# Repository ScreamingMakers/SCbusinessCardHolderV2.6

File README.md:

# SCbusinessCardHolderV2.6
V2.6 of the Screaming Circuits open source, hackable, electronic business card holder 

The Screaming Circuits business card holder is a multi-function device intended for your amusement and as a demonstration of our workmanship.

It has 19 LEDs along the bottom of the board, with 16 being broken out to optional headers - for your hacking pleasure. Along the top, it uses the two user buttons, and the I2C/SPI and ICSP headrs to hold the business cards.

V2.6 also has all eight bits of ports A and C brought out to .1" headers. Port bits D5/An25, D6/TX, D7/RX, B0/A12, and B3/CCP2 are brought out to a separate header.

Note that this kit uses a pair of CR1220 coin cell batteries. The silk screen erronously calls for CR2032 batteries. Oops. My bad.
Mechanical build instructions:

After soldering in the I2C and ICSP pin headers, attaching the rubber feet, and inserting the batteries, it’s ready to go. Place it on your desk and put about ten business cards in. When someone takes a card (or if you pound on your keyboard hard enough) some of the LEDs will flash.

If you tip it up, so that the LEDs run along the bottom, it will act as a spirit level, and as a short ruler. It’s not angle calibrated. Doing so is up to you.

The microcontroller fitted is of the Microchip PIC18F46K22 family. This run of V2.6 was produced with a PIC18F46K22. V2.5 had uses CR2032 batteries and came with the PIC18F43K22 – the same MCU, but with less FLASH and SRAM. The accelerometer is a Freescale MMA8452Q. The schematic and layout were created with EagleCAD. The code was written and compiled with Microchip XC8 in Mplab-X.

One of the pin headers is connected to the I2C and SPI bus pins on the MCU. The other is connected to the Microchip ICSP (in circuit serial programming) pins on the MCU. Button Usr 1 is connected to I/O pin RB4, and Usr 2 is connected to RB5.

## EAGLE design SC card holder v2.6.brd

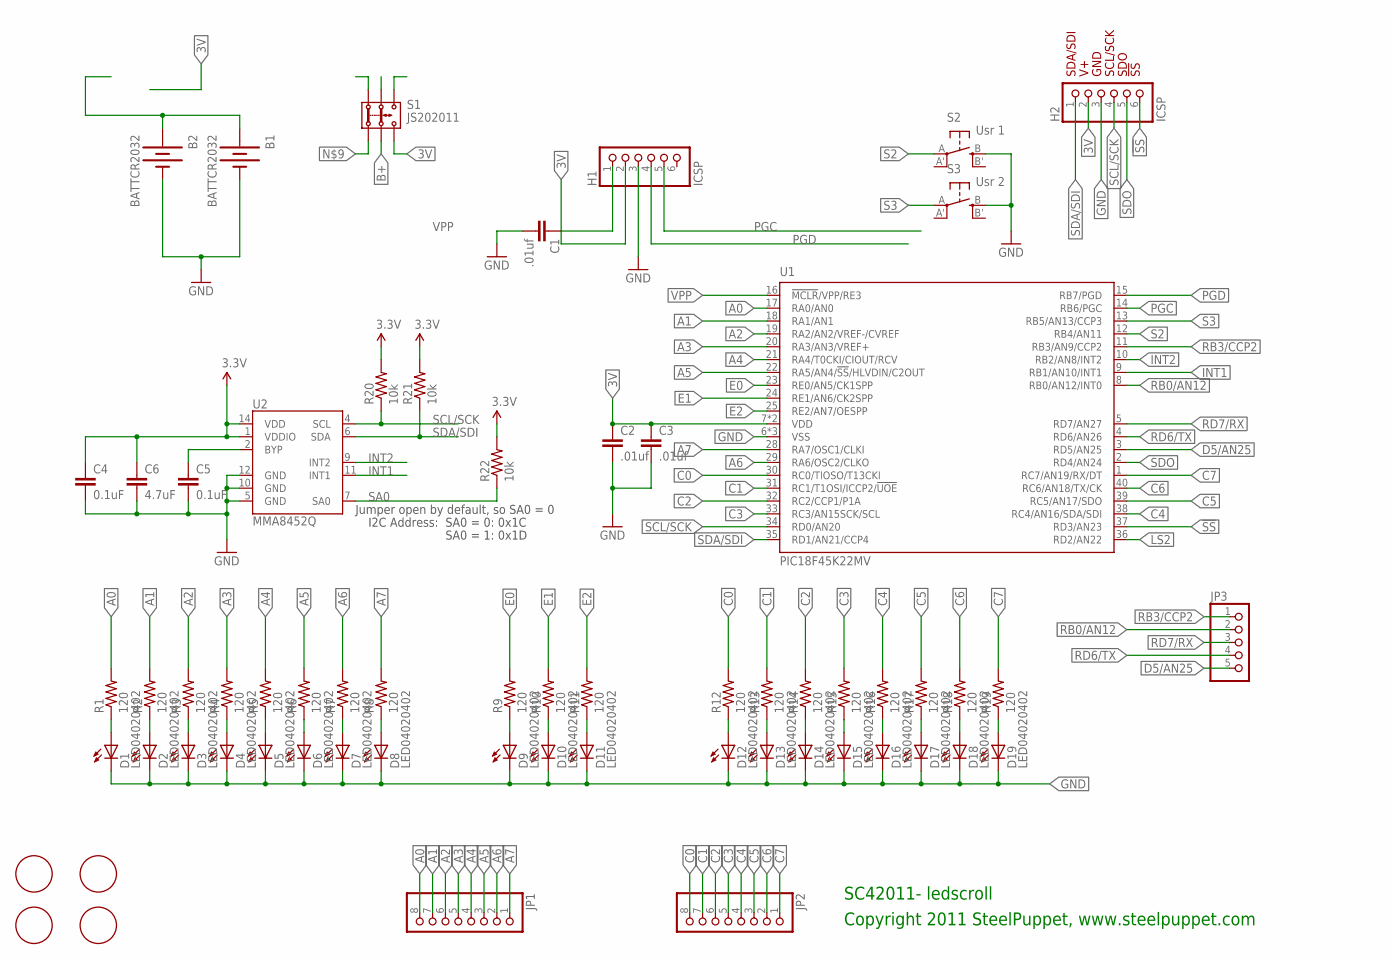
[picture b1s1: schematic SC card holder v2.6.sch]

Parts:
B1, B2: BATTCR2032; BATT_CR1220_SMT
C1, C2, C3: .01uf; 0402-CAP
C4, C5: 0.1uF; 0402-CAP
C6: 4.7uF; 0402-CAP
D1, D2, D3, D4, D5, D6, D7, D8, D9, D10, D11, D12, D13, D14, D15, D16, D17, D18, D19: LED04020402; LED0402
H1, H2: ICSP; 1X06-S
JP1, JP2: PINHD-1X08_2.54-S; 1X08-S
JP3: PINHD-1X05_2.54-S; 1X05-S
R1, R2, R3, R4, R5, R6, R7, R8, R9, R10, R11, R12, R13, R14, R15, R16, R17, R18, R19: 120; R0402
R20, R21, R22: 10k; 0402-RES
S1: JS202011; JS202011SMT
S2: Usr 1; EVQ-Q2
S3: Usr 2; EVQ-Q2
U1: PIC18F45K22MV; QFN40-5X5
U2: MMA8452Q; QFN-16_0.5MM
U$4, U$5, U$6, U$7: FID1.5

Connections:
3V: C2.1, C3.1, C4.1, C6.1, H1.2, H2.2, R20.2, R21.2, R22.2, S1.3 (3.2), S1.4 (3.1), U1.7 (VDD), U1.26 (VDD), U2.1 (VDDIO), U2.14 (VDD)
!SS: H2.6, U1.37 (RD3/AN23)
A0: JP1.8, R1.2, U1.17 (RA0/AN0)
A1: JP1.7, R2.2, U1.18 (RA1/AN1)
A2: JP1.6, R3.2, U1.19 (RA2/AN2/VREF-/CVREF)
A3: JP1.5, R4.2, U1.20 (RA3/AN3/VREF+)
A4: JP1.4, R5.2, U1.21 (RA4/T0CKI/CIOUT/RCV)
A5: JP1.3, R6.2, U1.22 (RA5/AN4/!SS!/HLVDIN/C2OUT)
A6: JP1.2, R7.2, U1.29 (RA6/OSC2/CLKO)
A7: JP1.1, R8.2, U1.28 (RA7/OSC1/CLKI)
B+: B1.1 (+), B1.3 (+), B2.1 (+), B2.3 (+), S1.2 (2.2), S1.5 (2.1)
BYP: C5.1, U2.2 (BYP)
C0: JP2.8, R12.2, U1.30 (RC0/TIOSO/T13CKI)
C1: JP2.7, R13.2, U1.31 (RC1/T1OSI/ICCP2/!UOE)
C2: JP2.6, R14.2, U1.32 (RC2/CCP1/P1A)
C3: JP2.5, R15.2, U1.33 (RC3/AN15SCK/SCL)
C4: JP2.4, R16.2, U1.38 (RC4/AN16/SDA/SDI)
C5: JP2.3, R17.2, U1.39 (RC5/AN17/SDO)
C6: JP2.2, R18.2, U1.40 (RC6/AN18/TX/CK)
C7: JP2.1, R19.2, U1.1 (RC7/AN19/RX/DT)
D5/AN25: JP3.5, U1.3 (RD5/AN25)
E0: R9.2, U1.23 (RE0/AN5/CK1SPP)
E1: R10.2, U1.24 (RE1/AN6/CK2SPP)
E2: R11.2, U1.25 (RE2/AN7/OESPP)
GND: B1.2 (-), B2.2 (-), C1.2, C2.2, C3.2, C4.2, C5.2, C6.2, D1.C, D2.C, D3.C, D4.C, D5.C, D6.C, D7.C, D8.C, D9.C, D10.C, D11.C, D12.C, D13.C, D14.C, D15.C, D16.C, D17.C, D18.C, D19.C, H1.3, H2.3, S2.B (S), S3.B (S), U1.6 (VSS), U1.27 (VSS), U1.41 (VSS), U2.5 (GND), U2.10 (GND), U2.12 (GND)
INT1: U1.9 (RB1/AN10/INT1), U2.11 (INT1)
INT2: U1.10 (RB2/AN8/INT2), U2.9 (INT2)
LS2: U1.36 (RD2/AN22)
unnamed: D1.A, R1.1
unnamed: D2.A, R2.1
unnamed: D3.A, R3.1
unnamed: D4.A, R4.1
unnamed: D9.A, R9.1
unnamed: D10.A, R10.1
unnamed: D11.A, R11.1
unnamed: D13.A, R13.1
unnamed: D14.A, R14.1
unnamed: D15.A, R15.1
unnamed: D12.A, R12.1
unnamed: D6.A, R6.1
unnamed: D7.A, R7.1
unnamed: D16.A, R16.1
unnamed: D17.A, R17.1
unnamed: D8.A, R8.1
unnamed: D5.A, R5.1
unnamed: D18.A, R18.1
unnamed: D19.A, R19.1
PGC: H1.5, U1.14 (RB6/PGC)
PGD: H1.4, U1.15 (RB7/PGD)
RB0/AN12: JP3.2, U1.8 (RB0/AN12/INT0)
RB3/CCP2: JP3.1, U1.11 (RB3/AN9/CCP2)
RD6/TX: JP3.4, U1.4 (RD6/AN26)
RD7/RX: JP3.3, U1.5 (RD7/AN27)
S2: S2.A, U1.12 (RB4/AN11)
S3: S3.A, U1.13 (RB5/AN13/CCP3)
SA0: R22.1, U2.7 (SA0)
SCL/SCK: H2.4, R20.1, U1.34 (RD0/AN20), U2.4 (SCL)
SDA/SDI: H2.1, R21.1, U1.35 (RD1/AN21/CCP4), U2.6 (SDA)
SDO: H2.5, U1.2 (RD4/AN24)
VPP: C1.1, H1.1, U1.16 (!MCLR!/VPP/RE3)

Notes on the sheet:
SC42011- ledscroll
Copyright 2011 SteelPuppet, www.steelpuppet.com
SDA/SDI
GND
SCL/SCK
SDO
!SS
I2C Address:
SA0 = 0: 0x1C
SA0 = 1: 0x1D
Jumper open by default, so SA0 = 0

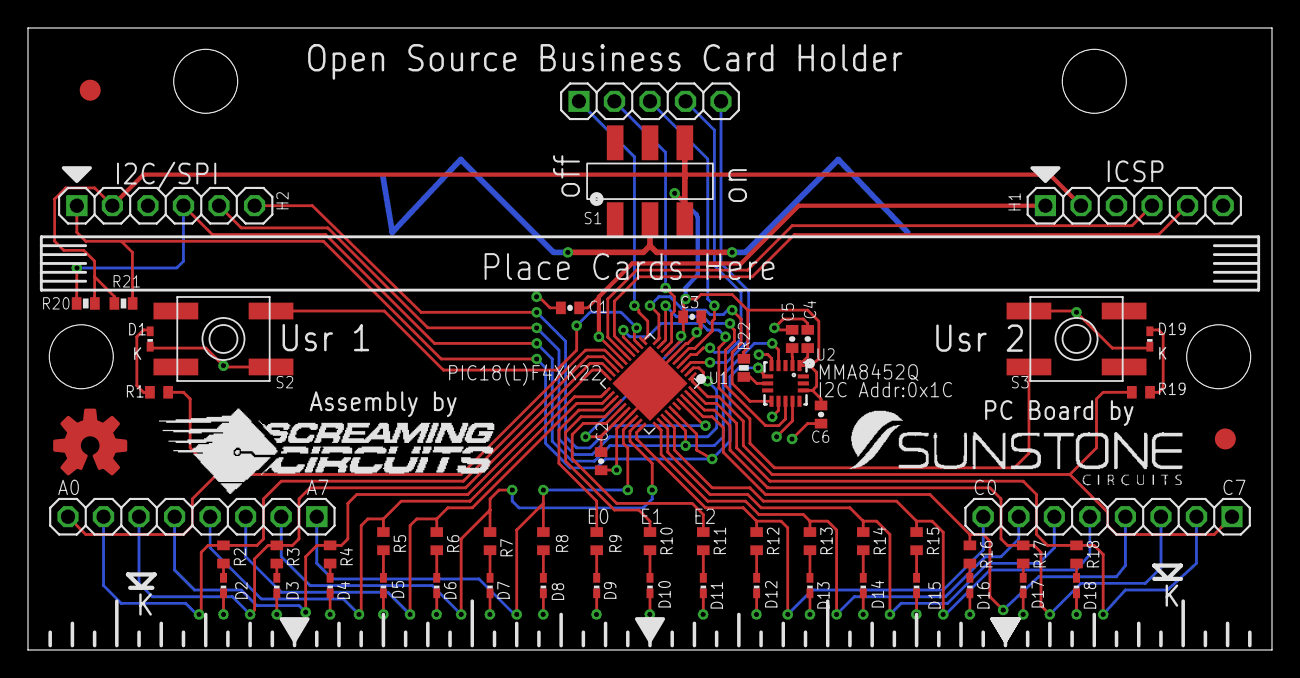
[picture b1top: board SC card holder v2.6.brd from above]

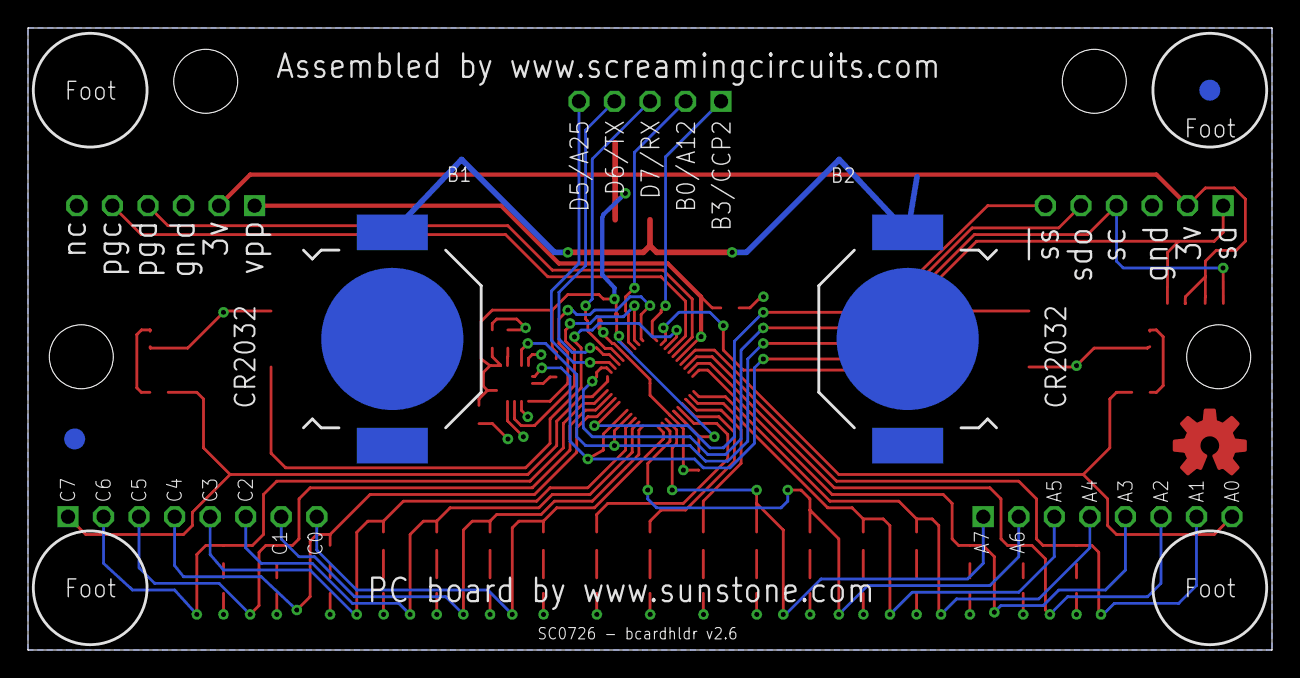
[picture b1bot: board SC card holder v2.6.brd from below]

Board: 2 copper layers, 88.9 x 44.5 mm, 66 parts (4 on the bottom side), 59 nets.

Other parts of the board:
U$1: SUNSTONE-LOGO
U$2: OSHWLOGO_TOP_0.2
U$3: SC-LOGO
